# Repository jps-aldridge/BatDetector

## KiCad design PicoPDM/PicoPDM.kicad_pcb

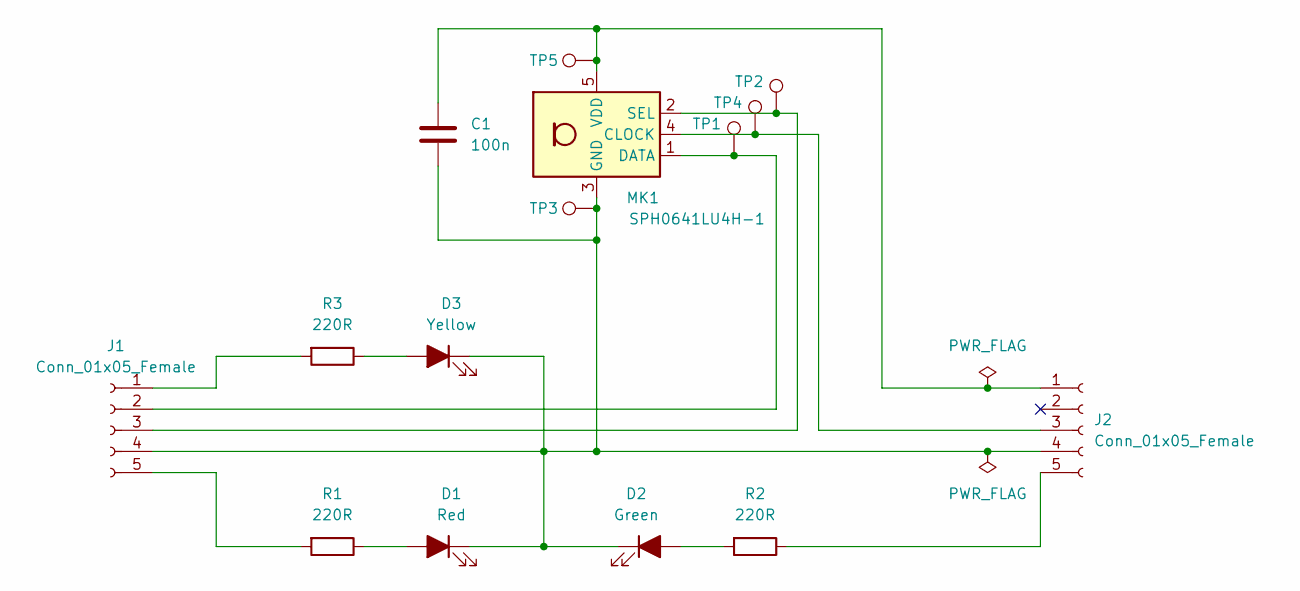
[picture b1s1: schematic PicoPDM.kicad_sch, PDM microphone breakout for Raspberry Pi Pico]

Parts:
C1: 100n; C_1206_3216Metric
D1: Red; LED_0603_1608Metric
D2: Green; LED_0603_1608Metric
D3: Yellow; LED_0603_1608Metric
J1, J2: Conn_01x05_Female; PinSocket_1x05_P2.54mm_Vertical
MK1: SPH0641LU4H-1; Knowles_LGA-5_3.5x2.65mm
R1, R2, R3: 220R; R_0603_1608Metric
TP1, TP2, TP3, TP4, TP5: TestPoint; SolderWire-0.1sqmm_1x01_D0.4mm_OD1mm

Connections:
unnamed: C1.1, J2.1, MK1.5 (VDD), TP5.1
unnamed: C1.2, D1.1 (K), D2.1 (K), D3.1 (K), J1.4, J2.4, MK1.3 (GND), TP3.1
unnamed: D1.2 (A), R1.1
unnamed: D2.2 (A), R2.2
unnamed: D3.2 (A), R3.1
unnamed: J1.1, R3.2
unnamed: J1.2, MK1.1 (DATA), TP1.1
unnamed: J1.3, MK1.2 (SEL), TP2.1
unnamed: J1.5, R1.2
unnamed: J2.3, MK1.4 (CLOCK), TP4.1
unnamed: J2.5, R2.1

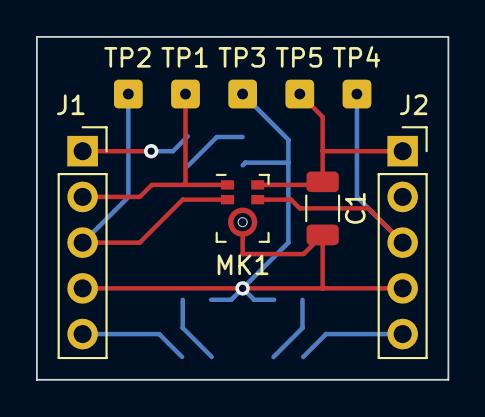
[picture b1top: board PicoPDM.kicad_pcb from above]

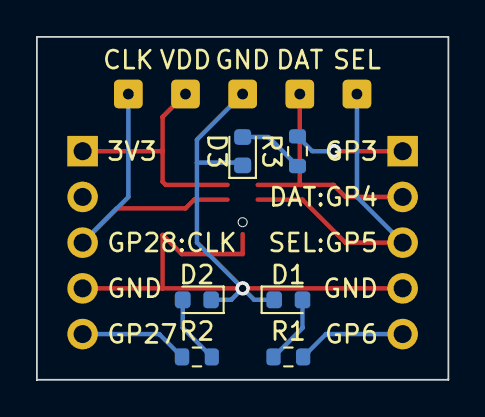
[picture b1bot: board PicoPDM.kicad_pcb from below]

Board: 2 copper layers, 22.9 x 19.1 mm, 15 parts (6 on the bottom side), 11 nets.

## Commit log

2022-05-04 PDM microphone breakout for Rasperry Pi Pico
